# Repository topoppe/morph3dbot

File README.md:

# Morph3DBot

Willkommen im GitHub-Repo von *Morph3DBot*

Alles zu diesem Projekt finden Sie unter [https://morph3dbot.de/](https://morph3dbot.de/)

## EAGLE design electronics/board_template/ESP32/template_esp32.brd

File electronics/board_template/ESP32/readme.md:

# ESP32 Board Template

Bei der ESP32 Platine handelt es sich um eine Arduino-IDE-Kompatible Basisplatine.
Diese Platine kann sowohl als Hauptplatine im System, als auch als Slave-Platine genutzt werden.

## Spannungsversorgung
Auf der Platine sind zwei Linearregler verbaut. Sie erzeugen aus der Versorgungsspannung des Systems stabile 5V und 3,3V Spannungsversorgungen für den Controller sowie weitere Peripherie.

## Controller
Herzstück der Platine ist ein ESP32-Wroom Modul von Espressif. Es ist der selbe Controller-Typ, der auch auf Node-MCU Boards verbaut ist.
Neben den Interfaces der AT-Mega-Platine bietet das Modul auch WLAN und Bluetooth Konnektivität.

## USB-Interface
Ein CP2104 Chip verbindet die UART-Schnittstelle des Controllers mit einer USB-Buchse. Hierüber ist eine Kommunikation mit einem PC und die Programmierung mittels der Arduino-IDE möglich.

## Erweiterungsschnittstelle
Auf der Oberseite der Platine sind zwei doppelreihige Buchsenleisten mit jeweils 12-Anschlüssen vorhanden. Hier können +5V, +3,3V, Ground, UART sowie die meisten Pins des Controllers abgegriffen werden.
So ist es möglich, eigene Erweiterungen anzuschließen.

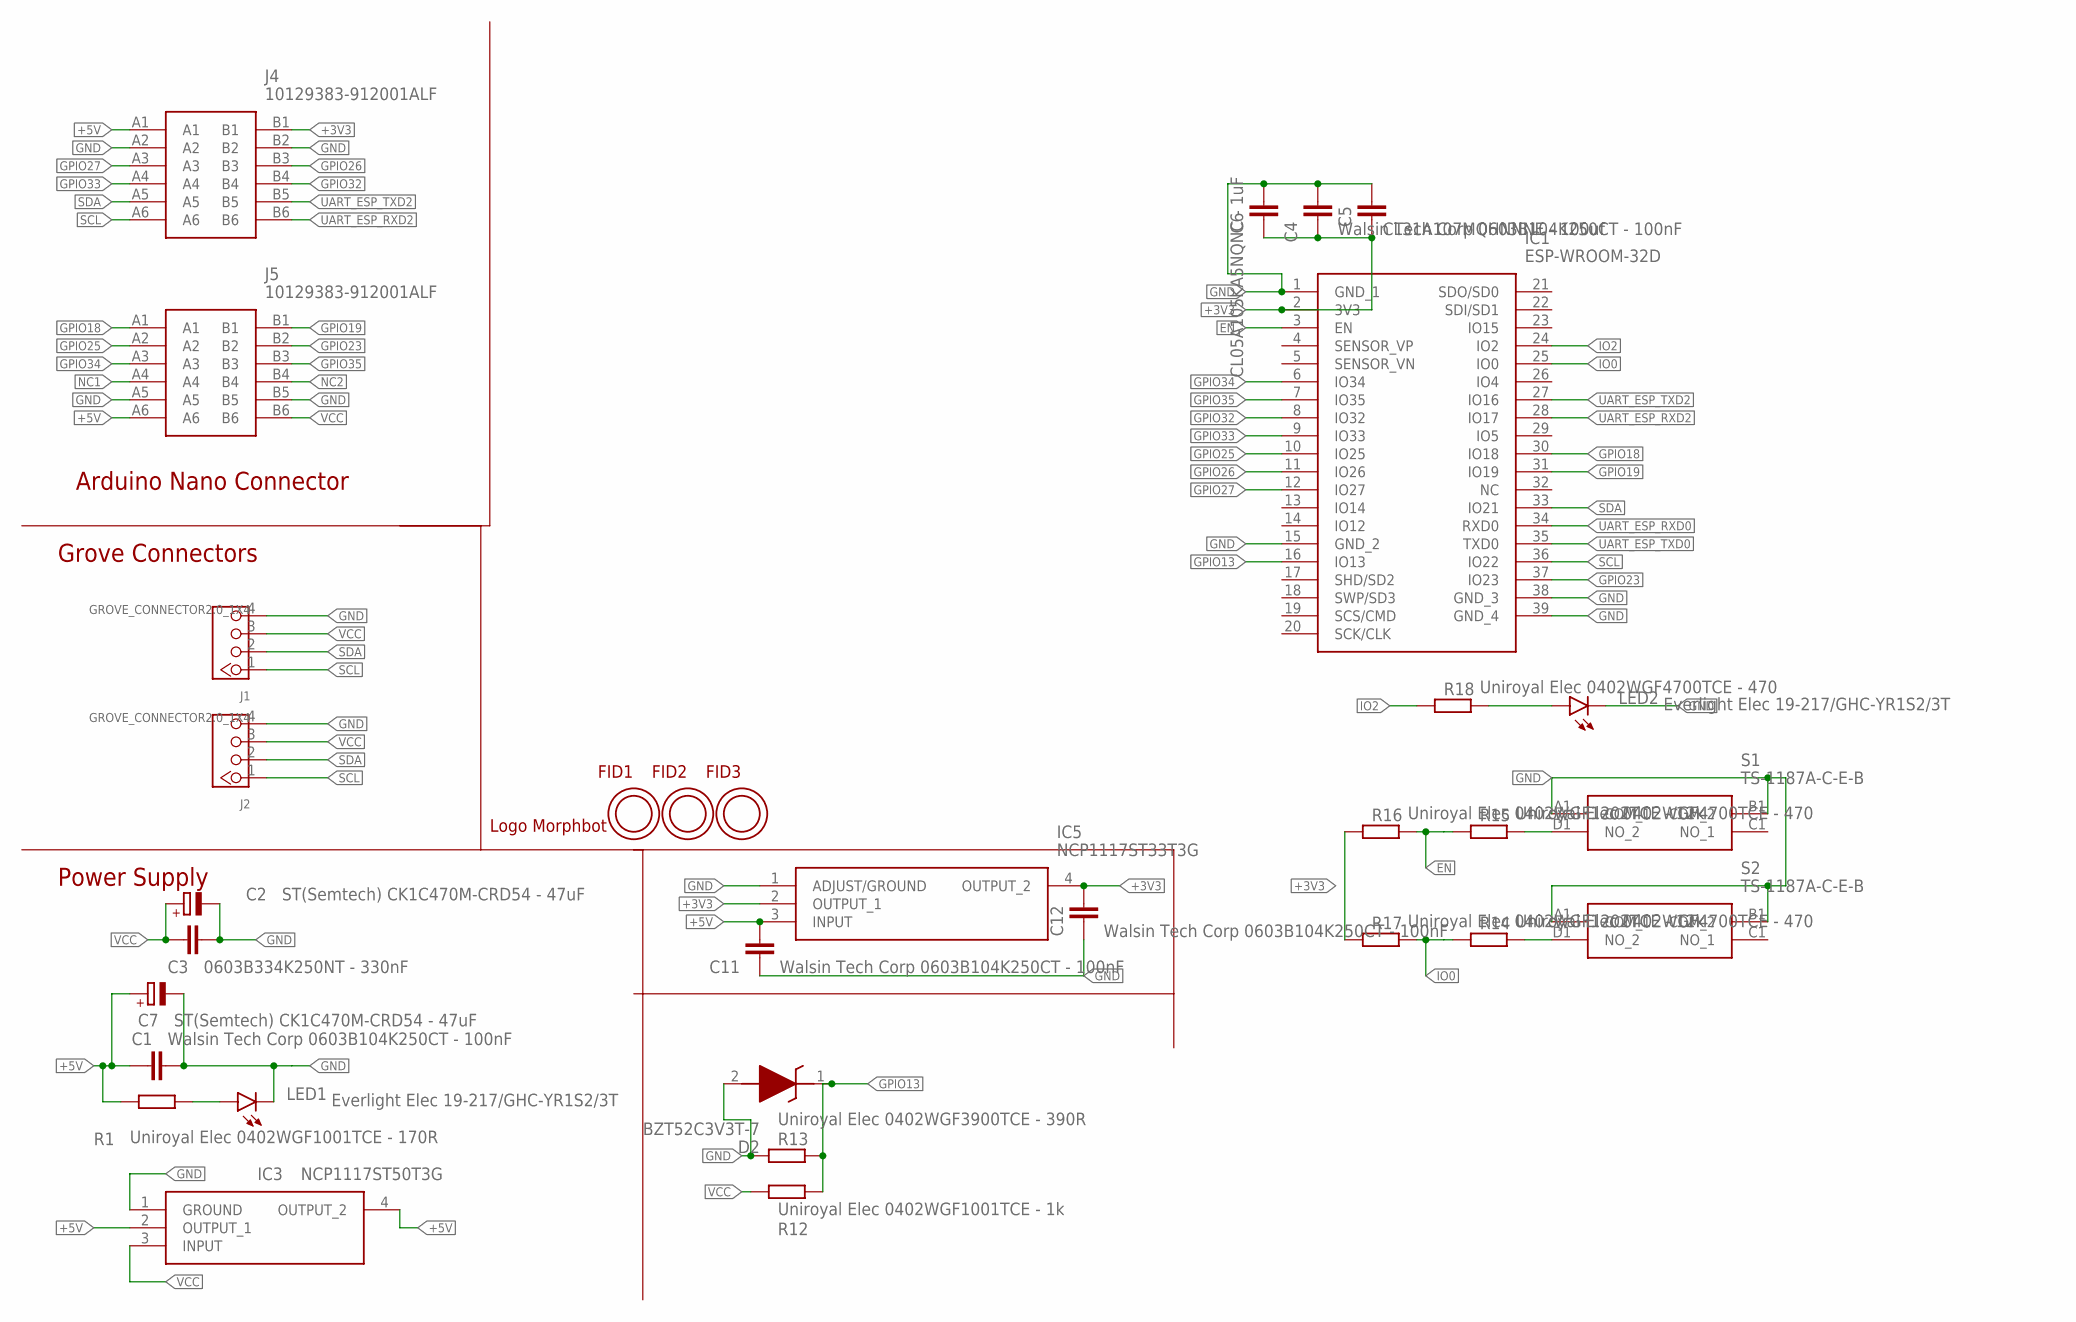
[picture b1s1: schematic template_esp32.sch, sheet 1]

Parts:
C1, C4, C11, C12: Walsin Tech Corp 0603B104K250CT - 100nF; C0603
C2, C7: ST(Semtech) CK1C470M-CRD54 - 47uF; PANASONIC_C
C3: 0603B334K250NT - 330nF; C0603
C5: CL31A107MQHNNNE - 100uf; C1206
C6: CL05A105KA5NQNC - 1uF; C0402
D2: BZT52C3V3T-7; SODFL1608X65N
FID1, FID2, FID3: OPEN-PNP-FIDUCIAL
IC1: ESP-WROOM-32D; ESPWROOM32D
IC3: NCP1117ST50T3G; SOT230P700X180-4N
IC5: NCP1117ST33T3G; SOT230P700X180-4N
J1, J2: GROVE_CONNECTOR2.0_1X4; 2.0_1X4_STRAIGHT
J4, J5: 10129383-912001ALF; 10129383912001ALF
LED1, LED2: Everlight Elec 19-217/GHC-YR1S2/3T; CHIPLED_0603
R1: Uniroyal Elec 0402WGF1001TCE - 170R; R0402
R12: Uniroyal Elec 0402WGF1001TCE - 1k; R0402
R13: Uniroyal Elec 0402WGF3900TCE - 390R; R0402
R14, R15, R18: Uniroyal Elec 0402WGF4700TCE - 470; R0402
R16, R17: Uniroyal Elec 0402WGF1202TCE - 12k; R0402
S1, S2: TS-1187A-C-E-B; TS1187ACEB
U$1: LOGO_MORPHBOT3MM; LOGO_MOPRHBOT_3MM

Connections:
+3V3: C4.1, C5.2, C6.1, C12.2, IC1.2 (3V3), IC5.2 (OUTPUT_1), IC5.4 (OUTPUT_2), J4.B1, R16.1, R17.1; also elsewhere on the board
+5V: C1.1, C7.+, C11.2, IC3.2 (OUTPUT_1), IC3.4 (OUTPUT_2), IC5.3 (INPUT), J4.A1, J5.A6, R1.2; also elsewhere on the board
EN: IC1.3 (EN), R15.1, R16.2; also elsewhere on the board
GND: C1.2, C2.-, C3.1, C4.2, C5.1, C6.2, C7.-, C11.1, C12.1, D2.2 (A), IC1.1 (GND_1), IC1.15 (GND_2), IC1.38 (GND_3), IC1.39 (GND_4), IC3.1 (GROUND), IC5.1 (ADJUST/GROUND), J1.4, J2.4, J4.A2, J4.B2, J5.A5, J5.B5, LED1.C, LED2.C, R13.1, S1.A1 (COM_1), S1.B1 (COM_2), S2.A1 (COM_1), S2.B1 (COM_2); also elsewhere on the board
GPIO13: D2.1 (K), IC1.16 (IO13), R12.1, R13.2
GPIO18: IC1.30 (IO18), J5.A1
GPIO19: IC1.31 (IO19), J5.B1
GPIO23: IC1.37 (IO23), J5.B2
GPIO25: IC1.10 (IO25), J5.A2
GPIO26: IC1.11 (IO26), J4.B3
GPIO27: IC1.12 (IO27), J4.A3
GPIO32: IC1.8 (IO32), J4.B4
GPIO33: IC1.9 (IO33), J4.A4
GPIO34: IC1.6 (IO34), J5.A3
GPIO35: IC1.7 (IO35), J5.B3
IO0: IC1.25 (IO0), R14.1, R17.2; also elsewhere on the board
IO2: IC1.24 (IO2), R18.1
unnamed: LED1.A, R1.1
unnamed: R15.2, S1.D1 (NO_2)
unnamed: R14.2, S2.D1 (NO_2)
unnamed: LED2.A, R18.2
NC1: J5.A4
NC2: J5.B4
SCL: IC1.36 (IO22), J1.1, J2.1, J4.A6
SDA: IC1.33 (IO21), J1.2, J2.2, J4.A5
UART_ESP_RXD0: IC1.34 (RXD0); also elsewhere on the board
UART_ESP_RXD2: IC1.28 (IO17), J4.B6
UART_ESP_TXD0: IC1.35 (TXD0); also elsewhere on the board
UART_ESP_TXD2: IC1.27 (IO16), J4.B5
VCC: C2.+, C3.2, IC3.3 (INPUT), J1.3, J2.3, J5.B6, R12.2; also elsewhere on the board

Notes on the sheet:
Power Supply
Grove Connectors
Arduino Nano Connector

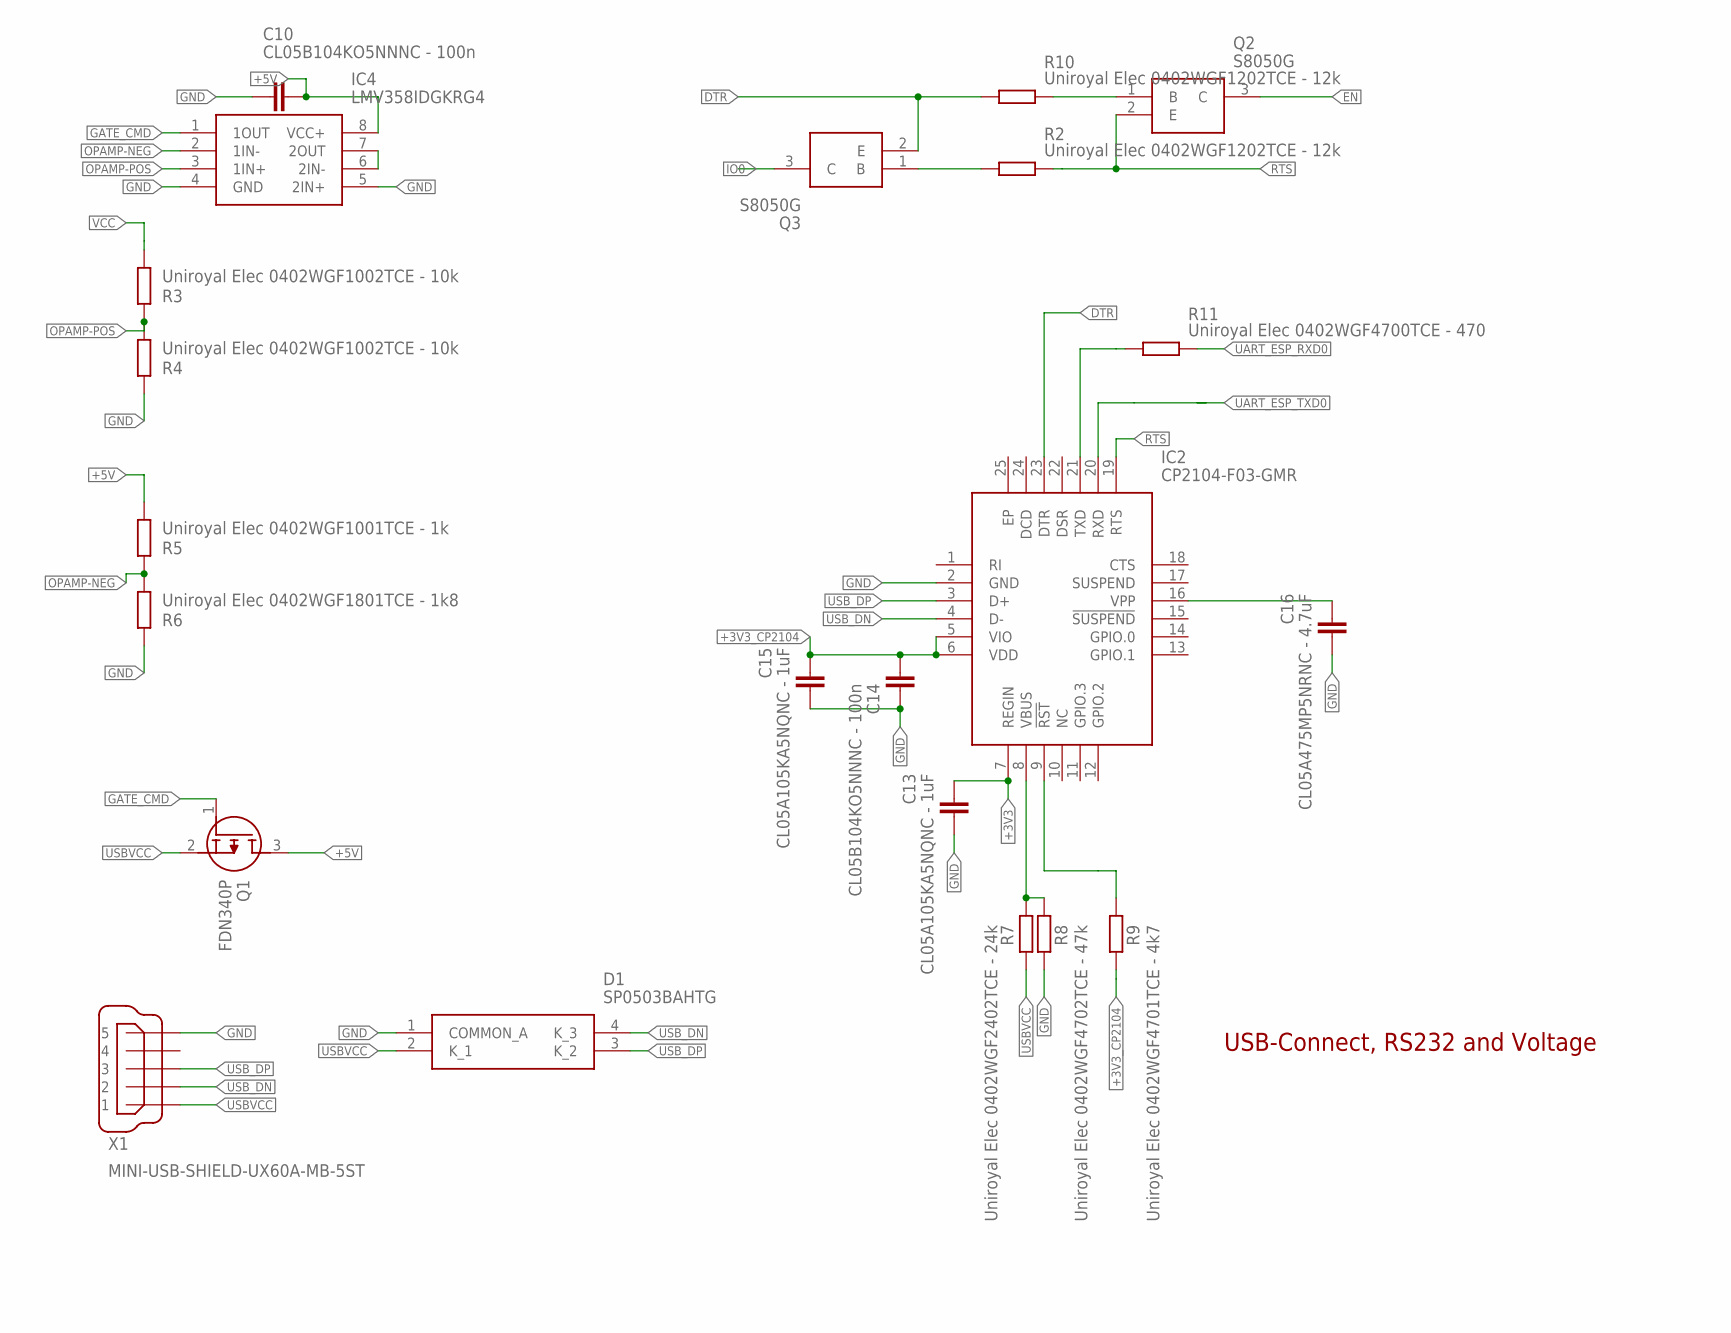
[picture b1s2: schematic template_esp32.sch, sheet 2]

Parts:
C10, C14: CL05B104KO5NNNC - 100n; C0402
C13, C15: CL05A105KA5NQNC - 1uF; C0402
C16: CL05A475MP5NRNC - 4.7uF; C0402
D1: SP0503BAHTG
IC2: CP2104-F03-GMR; QFN50P400X400X80-25N
IC4: LMV358IDGKRG4; SOP65P490X110-8N
Q1: FDN340P; SOT95P237X112-3N
Q2, Q3: S8050G; SOT95P240X110-3N
R2, R10: Uniroyal Elec 0402WGF1202TCE - 12k; R0402
R3, R4: Uniroyal Elec 0402WGF1002TCE - 10k; R0402
R5: Uniroyal Elec 0402WGF1001TCE - 1k; R0402
R6: Uniroyal Elec 0402WGF1801TCE - 1k8; R0402
R7: Uniroyal Elec 0402WGF2402TCE - 24k; R0402
R8: Uniroyal Elec 0402WGF4702TCE - 47k; R0402
R9: Uniroyal Elec 0402WGF4701TCE - 4k7; R0402
R11: Uniroyal Elec 0402WGF4700TCE - 470; R0402
X1: MINI-USB-SHIELD-UX60A-MB-5ST; UX60A-MB-5ST

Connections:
+3V3: C13.2, IC2.7 (REGIN); also elsewhere on the board
+3V3_CP2104: C14.2, C15.2, IC2.5 (VIO), IC2.6 (VDD), R9.2
+5V: C10.2, IC4.8 (VCC+), Q1.3 (D), R5.1; also elsewhere on the board
DTR: IC2.23 (DTR), Q3.2 (E), R10.1
EN: Q2.3 (C); also elsewhere on the board
GATE_CMD: IC4.1 (1OUT), Q1.1 (G)
GND: C10.1, C13.1, C14.1, C15.1, C16.1, D1.1 (COMMON_A), IC2.2 (GND), IC4.4 (GND), IC4.5 (2IN+), R4.2, R6.2, R8.2, X1.5; also elsewhere on the board
IO0: Q3.3 (C); also elsewhere on the board
unnamed: Q3.1 (B), R2.1
unnamed: IC4.6 (2IN-), IC4.7 (2OUT)
unnamed: IC2.8 (VBUS), R7.1, R8.1
unnamed: IC2.9 (!RST), R9.1
unnamed: C16.2, IC2.16 (VPP)
unnamed: IC2.21 (TXD), R11.1
unnamed: Q2.1 (B), R10.2
OPAMP-NEG: IC4.2 (1IN-), R5.2, R6.1
OPAMP-POS: IC4.3 (1IN+), R3.2, R4.1
RTS: IC2.19 (RTS), Q2.2 (E), R2.2
UART_ESP_RXD0: R11.2; also elsewhere on the board
UART_ESP_TXD0: IC2.20 (RXD); also elsewhere on the board
USBVCC: D1.2 (K_1), Q1.2 (S), R7.2, X1.1
USB_DN: D1.4 (K_3), IC2.4 (D-), X1.2
USB_DP: D1.3 (K_2), IC2.3 (D+), X1.3
VCC: R3.1; also elsewhere on the board

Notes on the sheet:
USB-Connect, RS232 and Voltage

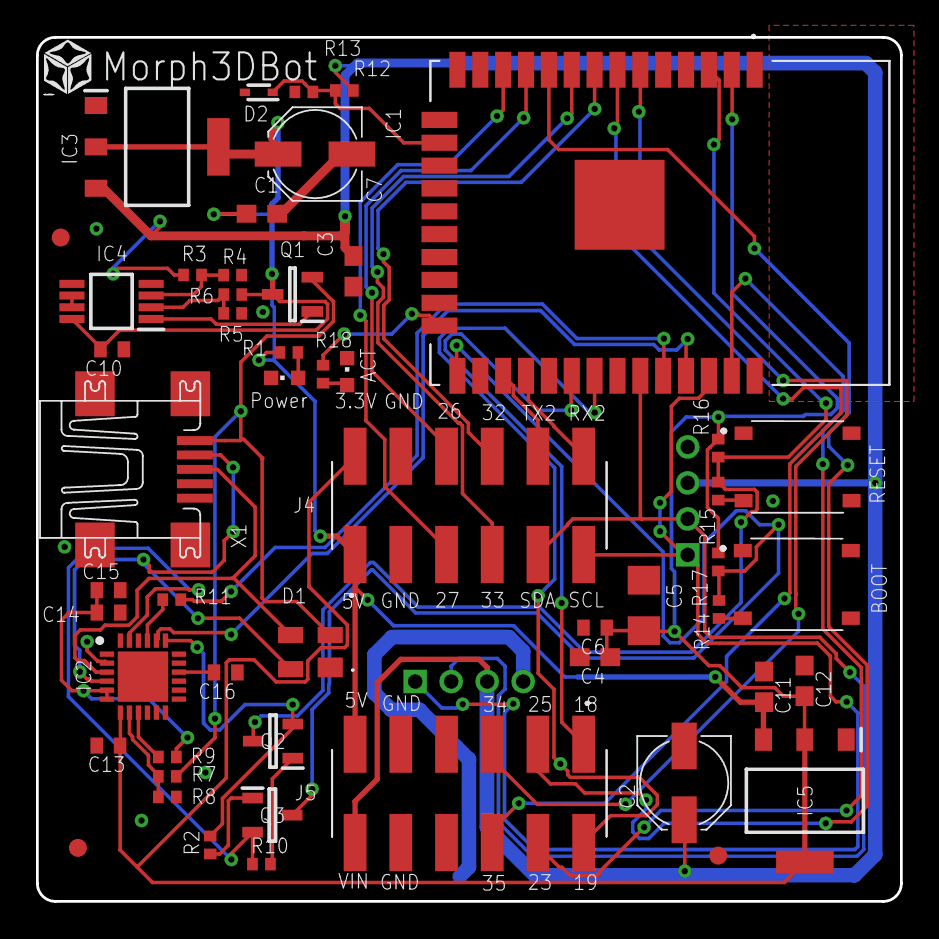
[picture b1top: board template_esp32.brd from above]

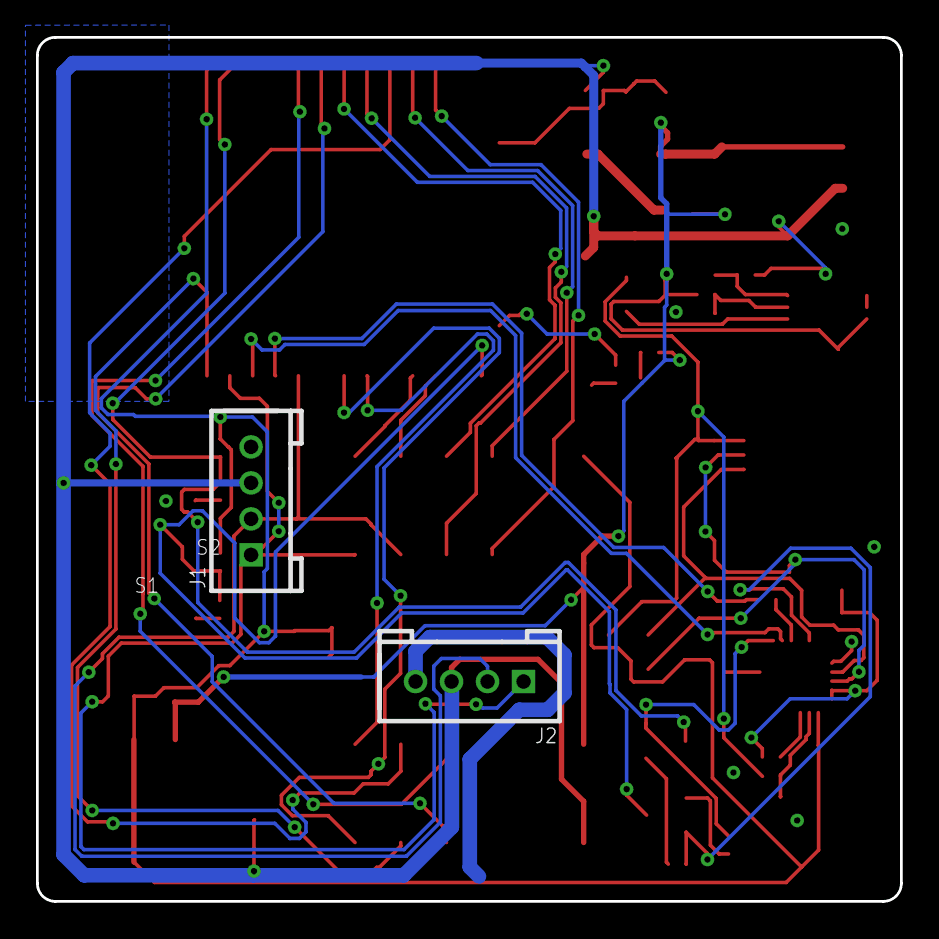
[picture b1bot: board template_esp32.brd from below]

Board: 2 copper layers, 48.0 x 48.0 mm, 55 parts (2 on the bottom side), 44 nets.

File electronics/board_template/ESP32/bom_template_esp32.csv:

"Qty";"Value";"Device";"Package";"Parts";"Description";"ARROW_PART_NUMBER";"ARROW_PRICE-STOCK";"DESCRIPTION";"HEIGHT";"MANUFACTURER_NAME";"MANUFACTURER_PART_NUMBER";"MF";"MOUSER_PART_NUMBER";"MOUSER_PRICE-STOCK";"MPN";"OC_FARNELL";"OC_NEWARK";"POPULARITY";"SPICEPREFIX";
"1";"0603B334K250NT - 330nF";"C-EUC0603";"C0603";"C3";"CAPACITOR, European symbol";"";"";"";"";"";"";"";"";"";"";"";"";"73";"C";
"2";"10129383-912001ALF";"10129383-912001ALF";"10129383912001ALF";"J4, J5";"EconoStik, Board to Board connector, Unshrouded Vertical Header, Surface Mount, Double Row,  Positions, 2.54 mm (0.100in) Pitch.";"";"";"EconoStik, Board to Board connector, Unshrouded Vertical Header, Surface Mount, Double Row,  Positions, 2.54 mm (0.100in) Pitch.";"8.58mm";"Amphenol";"10129383-912001ALF";"";"649-1012938391201ALF";"https://www.mouser.co.uk/ProductDetail/Amphenol-FCI/10129383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";"";"";"";"";"";
"1";"BZT52C3V3T-7";"BZT52C3V3T-7";"SODFL1608X65N";"D2";"Diodes Inc BZT52C3V3T-7 Zener Diode, 3.3V 6% 300 mW SMT 2-Pin SOD-523";"BZT52C3V3T-7";"https://www.arrow.com/en/products/bzt52c3v3t-7/diodes-incorporated";"Diodes Inc BZT52C3V3T-7 Zener Diode, 3.3V 6% 300 mW SMT 2-Pin SOD-523";"0.65mm";"Diodes Inc.";"BZT52C3V3T-7";"";"621-BZT52C3V3T-7";"https://www.mouser.co.uk/ProductDetail/Diodes-Incorporated/B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";"";"";"";"";"";
"3";"CL05A105KA5NQNC - 1uF";"C-EUC0402";"C0402";"C6, C13, C15";"CAPACITOR, European symbol";"";"";"";"";"";"";"";"";"";"";"";"";"18";"C";
"1";"CL05A475MP5NRNC - 4.7uF";"C-EUC0402";"C0402";"C16";"CAPACITOR, European symbol";"";"";"";"";"";"";"";"";"";"";"";"";"18";"C";
"2";"CL05B104KO5NNNC - 100n";"C-EUC0402";"C0402";"C10, C14";"CAPACITOR, European symbol";"";"";"";"";"";"";"";"";"";"";"";"";"18";"C";
"1";"CL31A107MQHNNNE - 100uf";"C-EUC1206";"C1206";"C5";"CAPACITOR, European symbol";"";"";"";"";"";"";"";"";"";"";"";"";"54";"C";
"1";"CP2104-F03-GMR";"CP2104-F03-GMR";"QFN50P400X400X80-25N";"IC2";"USB-to-UART 1-CH 576byte FIFO 3.3V Automotive 24-Pin QFN EP T/R";"CP2104-F03-GMR";"https://www.arrow.com/en/products/cp2104-f03-gmr/silicon-labs";"USB-to-UART 1-CH 576byte FIFO 3.3V Automotive 24-Pin QFN EP T/R";"0.8mm";"Silicon Labs";"CP2104-F03-GMR";"";"634-CP2104-F03-GMR";"https://www.mouser.co.uk/ProductDetail/Silicon-Labs/CP2104-F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";"";"";"";"";"";
"1";"ESP-WROOM-32D";"ESP-WROOM-32D";"ESPWROOM32D";"IC1";"WiFi Modules (802.11) ESP32-D0WD 32 Mbits, 3.3 V 40 MHz onboard antenna (18.00+/-0.10) x (25.50+/-0.10) x (3.10+/-0.10)";"";"";"WiFi Modules (802.11) ESP32-D0WD 32 Mbits, 3.3 V 40 MHz onboard antenna (18.00+/-0.10) x (25.50+/-0.10) x (3.10+/-0.10)";"3.2mm";"Espressif Systems";"ESP-WROOM-32D";"";"356-ESP-WROOM-32D";"https://www.mouser.com/Search/Refine.aspx?Keyword=356-ESP-WROOM-32D";"";"";"";"";"";
"2";"Everlight Elec 19-217/GHC-YR1S2/3T";"LEDCHIPLED_0603";"CHIPLED_0603";"LED1, LED2";"LED";"";"";"";"";"";"";"";"";"";"";"";"";"28";"";
"1";"FDN340P";"FDN340P";"SOT95P237X112-3N";"Q1";"Trans MOSFET P-CH 20V 2A 3-Pin SuperSOT";"FDN340P";"https://www.arrow.com/en/products/fdn340p/on-semiconductor";"Trans MOSFET P-CH 20V 2A 3-Pin SuperSOT";"1.12mm";"ON Semiconductor";"FDN340P";"";"512-FDN340P";"https://www.mouser.co.uk/ProductDetail/ON-Semiconductor-Fair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";"";"";"";"";"";
"2";"GROVE_CONNECTOR2.0_1X4";"GROVE_CONNECTOR2.0_1X4";"2.0_1X4_STRAIGHT";"J1, J2";"Seeedstudio Grove-Connector:";"";"";"";"";"";"";"";"";"";"";"";"";"";"";
"1";"LMV358IDGKRG4";"LMV358IDGKRG4";"SOP65P490X110-8N";"IC4";"Operational Amplifiers - Op Amps Dual Low-Voltage Rail-to-Rail Out";"LMV358IDGKRG4";"https://www.arrow.com/en/products/lmv358idgkrg4/texas-instruments";"Operational Amplifiers - Op Amps Dual Low-Voltage Rail-to-Rail Out";"1.1mm";"Texas Instruments";"LMV358IDGKRG4";"";"595-LMV358IDGKRG4";"https://www.mouser.co.uk/ProductDetail/Texas-Instruments/LMV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";"";"";"";"";"";
"1";"LOGO_MORPHBOT3MM";"LOGO_MORPHBOT3MM";"LOGO_MOPRHBOT_3MM";"U$1";"";"";"";"";"";"";"";"";"";"";"";"";"";"";"";
"1";"MINI-USB-SHIELD-UX60A-MB-5ST";"MINI-USB-SHIELD-UX60A-MB-5ST";"UX60A-MB-5ST";"X1";"MINI USB Connector";"";"";"";"";"";"";"";"";"";"";"unknown";"unknown";"0";"";
"1";"NCP1117ST33T3G";"NCP1117ST33T3G";"SOT230P700X180-4N";"IC5";"ON SEMICONDUCTOR - NCP1117ST33T3G - IC, LINEAR VOLTAGE REGULATOR";"NCP1117ST33T3G";"https://www.arrow.com/en/products/ncp1117st33t3g/on-semiconductor";"ON SEMICONDUCTOR - NCP1117ST33T3G - IC, LINEAR VOLTAGE REGULATOR";"1.8mm";"ON Semiconductor";"NCP1117ST33T3G";"";"863-NCP1117ST33T3G";"https://www.mouser.co.uk/ProductDetail/ON-Semiconductor/NCP1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";"";"";"";"";"";
"1";"NCP1117ST50T3G";"NCP1117ST50T3G";"SOT230P700X180-4N";"IC3";"ON SEMICONDUCTOR - NCP1117ST50T3G - LDO, REG, 20VIN, 1A, 5V, 1%, SOT223-3";"NCP1117ST50T3G";"https://www.arrow.com/en/products/ncp1117st50t3g/on-semiconductor";"ON SEMICONDUCTOR - NCP1117ST50T3G - LDO, REG, 20VIN, 1A, 5V, 1%, SOT223-3";"1.8mm";"ON Semiconductor";"NCP1117ST50T3G";"";"863-NCP1117ST50T3G";"https://www.mouser.co.uk/ProductDetail/ON-Semiconductor/NCP1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";"";"";"";"";"";
"3";"OPEN-PNP-FIDUCIAL";"OPEN-PNP-FIDUCIAL";"OPEN-PNP-FIDUCIAL";"FID1, FID2, FID3";"";"";"";"";"";"";"";"";"";"";"";"";"";"";"";
"2";"S8050G";"S8050G";"SOT95P240X110-3N";"Q2, Q3";"Silicon Epitaxial Planar Transistor";"";"";"Silicon Epitaxial Planar Transistor";"1.1mm";"Galaxy";"S8050G";"";"";"";"";"";"";"";"";
"1";"SP0503BAHTG";"SP0503BAHTG";"SP0503BAHTG";"D1";"ESD Suppressors / TVS Diodes TVS AVAL DIODE SMT";"SP0503BAHTG";"https://www.arrow.com/en/products/sp0503bahtg/littelfuse";"ESD Suppressors / TVS Diodes TVS AVAL DIODE SMT";"1.22mm";"LITTELFUSE";"SP0503BAHTG";"";"576-SP0503BAHTG";"https://www.mouser.co.uk/ProductDetail/Littelfuse/SP0503BAHT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";"";"";"";"";"";
"2";"ST(Semtech) CK1C470M-CRD54 - 47uF";"CPOL-EUC";"PANASONIC_C";"C2, C7";"POLARIZED CAPACITOR, European symbol";"";"";"";"";"";"";"";"";"";"";"";"";"4";"C";
"2";"TS-1187A-C-E-B";"TS-1187A-C-E-B";"TS1187ACEB";"S1, S2";"SPST 50mA @ 12VDC 5.10mm x 5.10mm SMD Tactile Switches RoHS";"";"";"SPST 50mA @ 12VDC 5.10mm x 5.10mm SMD Tactile Switches RoHS";"1.65mm";"XKB Enterprise";"TS-1187A-C-E-B";"";"";"";"";"";"";"";"";
"1";"Uniroyal Elec 0402WGF1001TCE - 170R";"R-EU_R0402";"R0402";"R1";"RESISTOR, European symbol";"";"";"";"";"";"";"";"";"";"";"";"";"0";"R";
"2";"Uniroyal Elec 0402WGF1001TCE - 1k";"R-EU_R0402";"R0402";"R5, R12";"RESISTOR, European symbol";"";"";"";"";"";"";"";"";"";"";"";"";"0";"R";
"2";"Uniroyal Elec 0402WGF1002TCE - 10k";"R-EU_R0402";"R0402";"R3, R4";"RESISTOR, European symbol";"";"";"";"";"";"";"";"";"";"";"";"";"0";"R";
"4";"Uniroyal Elec 0402WGF1202TCE - 12k";"R-EU_R0402";"R0402";"R2, R10, R16, R17";"RESISTOR, European symbol";"";"";"";"";"";"";"";"";"";"";"";"";"0";"R";
"1";"Uniroyal Elec 0402WGF1801TCE - 1k8";"R-EU_R0402";"R0402";"R6";"RESISTOR, European symbol";"";"";"";"";"";"";"";"";"";"";"";"";"0";"R";
"1";"Uniroyal Elec 0402WGF2402TCE - 24k";"R-EU_R0402";"R0402";"R7";"RESISTOR, European symbol";"";"";"";"";"";"";"";"";"";"";"";"";"0";"R";
"1";"Uniroyal Elec 0402WGF3900TCE - 390R";"R-EU_R0402";"R0402";"R13";"RESISTOR, European symbol";"";"";"";"";"";"";"";"";"";"";"";"";"0";"R";
"4";"Uniroyal Elec 0402WGF4700TCE - 470";"R-EU_R0402";"R0402";"R11, R14, R15, R18";"RESISTOR, European symbol";"";"";"";"";"";"";"";"";"";"";"";"";"0";"R";
"1";"Uniroyal Elec 0402WGF4701TCE - 4k7";"R-EU_R0402";"R0402";"R9";"RESISTOR, European symbol";"";"";"";"";"";"";"";"";"";"";"";"";"0";"R";
"1";"Uniroyal Elec 0402WGF4702TCE - 47k";"R-EU_R0402";"R0402";"R8";"RESISTOR, European symbol";"";"";"";"";"";"";"";"";"";"";"";"";"0";"R";
"4";"Walsin Tech Corp 0603B104K250CT - 100nF";"C-EUC0603";"C0603";"C1, C4, C11, C12";"CAPACITOR, European symbol";"";"";"";"";"";"";"";"";"";"";"";"";"73";"C";

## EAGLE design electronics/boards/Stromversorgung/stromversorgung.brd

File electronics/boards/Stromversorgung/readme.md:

# Stromversorgungsplatine

**Diese Platine darf und muss genau einmal im System verbaut werden!**

Diese Platine dient zum Anschluss einer Stromquelle an das *Morph3DBot*-System. Hierzu dient eine Doppelschraubklemme auf der Oberseite der Platine.
Es können Spannungen bis zu 16 Volt eingespeist werden, es wird jedoch mindestens eine Spannung von 7 Volt benötigt.

Außerdem sind auf dieser Platine die Pull-Up-Widerstände für den I2C-Bus verbaut.

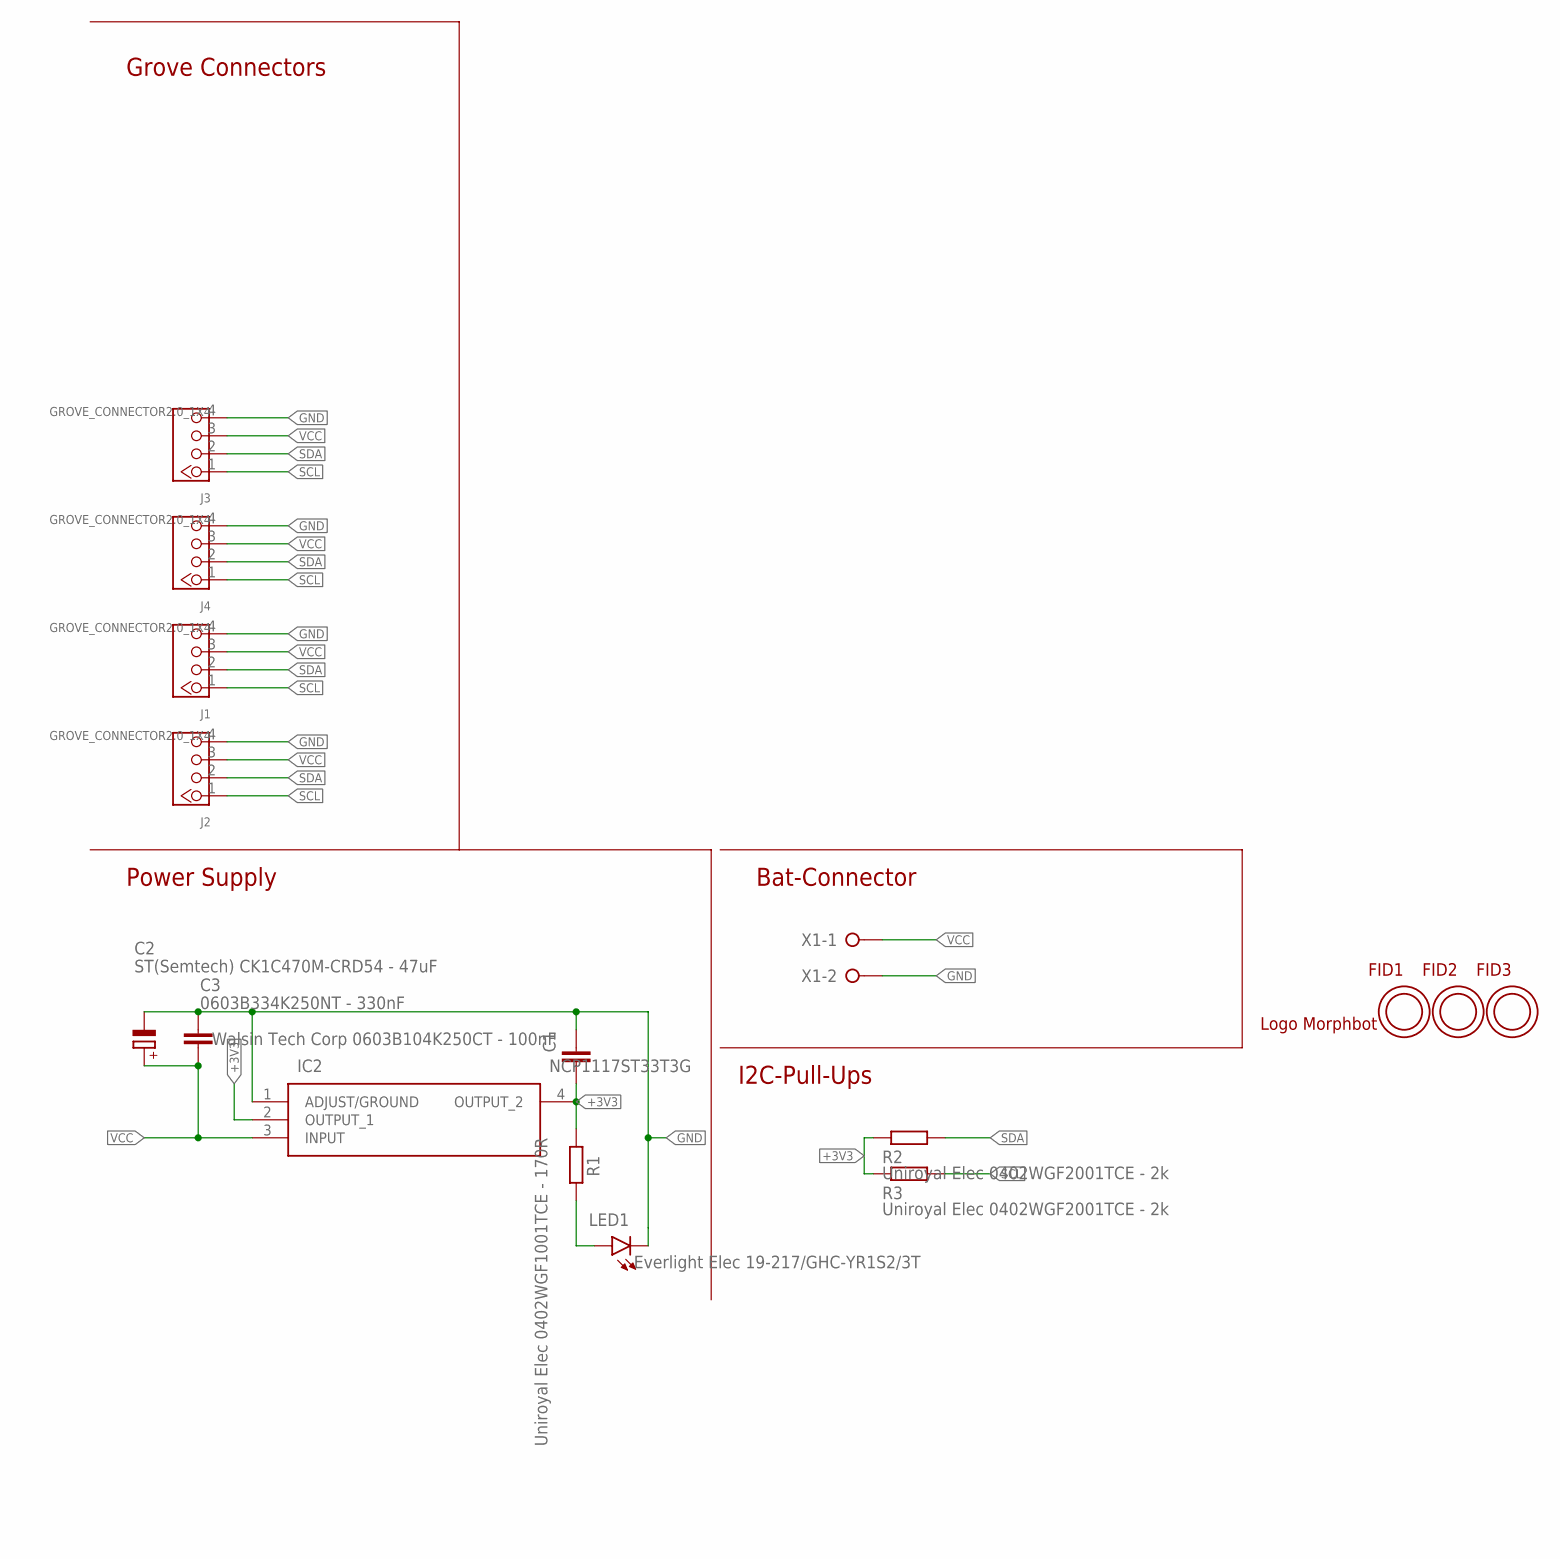
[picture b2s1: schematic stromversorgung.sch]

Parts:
C1: Walsin Tech Corp 0603B104K250CT - 100nF; C0603
C2: ST(Semtech) CK1C470M-CRD54 - 47uF; PANASONIC_C
C3: 0603B334K250NT - 330nF; C0603
FID1, FID2, FID3: OPEN-PNP-FIDUCIAL
IC2: NCP1117ST33T3G; SOT230P700X180-4N
J1, J2, J3, J4: GROVE_CONNECTOR2.0_1X4; 2.0_1X4_STRAIGHT
LED1: Everlight Elec 19-217/GHC-YR1S2/3T; CHIPLED_0603
R1: Uniroyal Elec 0402WGF1001TCE - 170R; R0402
R2, R3: Uniroyal Elec 0402WGF2001TCE - 2k; R0402
U$1: LOGO_MORPHBOT5MM; LOGO_MORPHBOT
X1: W237-02P; W237-132

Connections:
+3V3: C1.1, IC2.2 (OUTPUT_1), IC2.4 (OUTPUT_2), R1.2, R2.2, R3.2
GND: C1.2, C2.-, C3.1, IC2.1 (ADJUST/GROUND), J1.4, J2.4, J3.4, J4.4, LED1.C, X1.2
unnamed: LED1.A, R1.1
SCL: J1.1, J2.1, J3.1, J4.1, R3.1
SDA: J1.2, J2.2, J3.2, J4.2, R2.1
VCC: C2.+, C3.2, IC2.3 (INPUT), J1.3, J2.3, J3.3, J4.3, X1.1

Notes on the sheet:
Power Supply
Grove Connectors
I2C-Pull-Ups
Bat-Connector

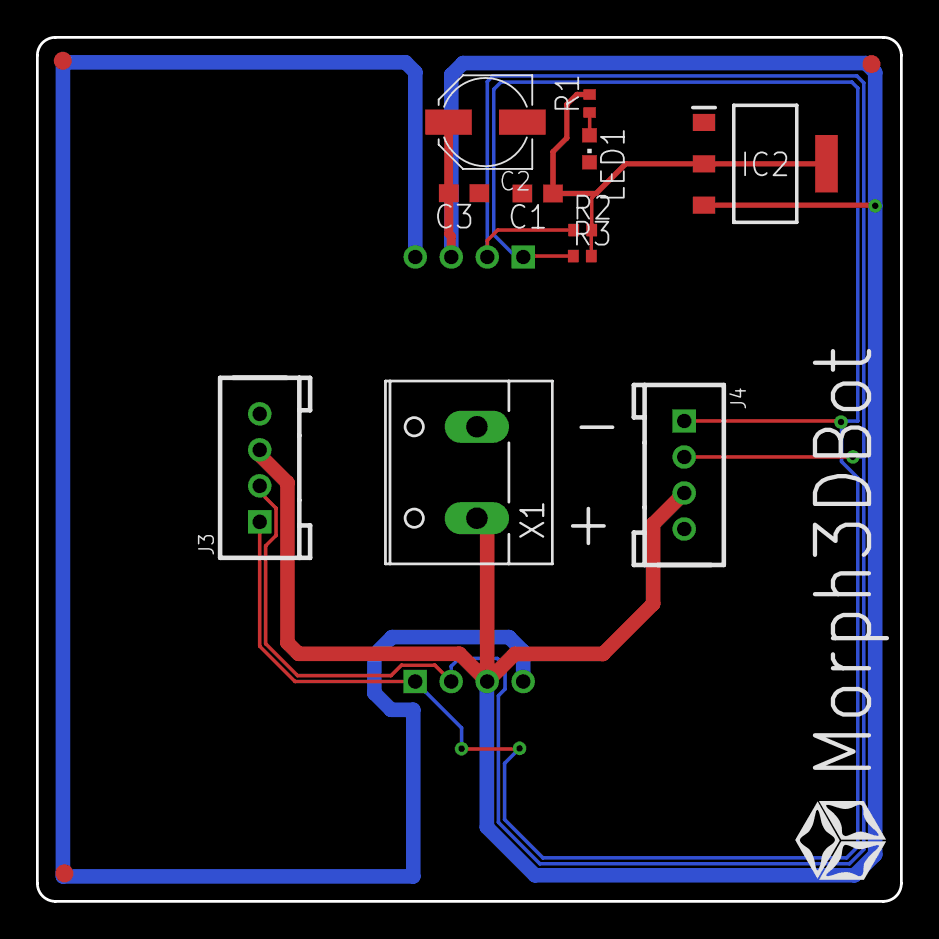
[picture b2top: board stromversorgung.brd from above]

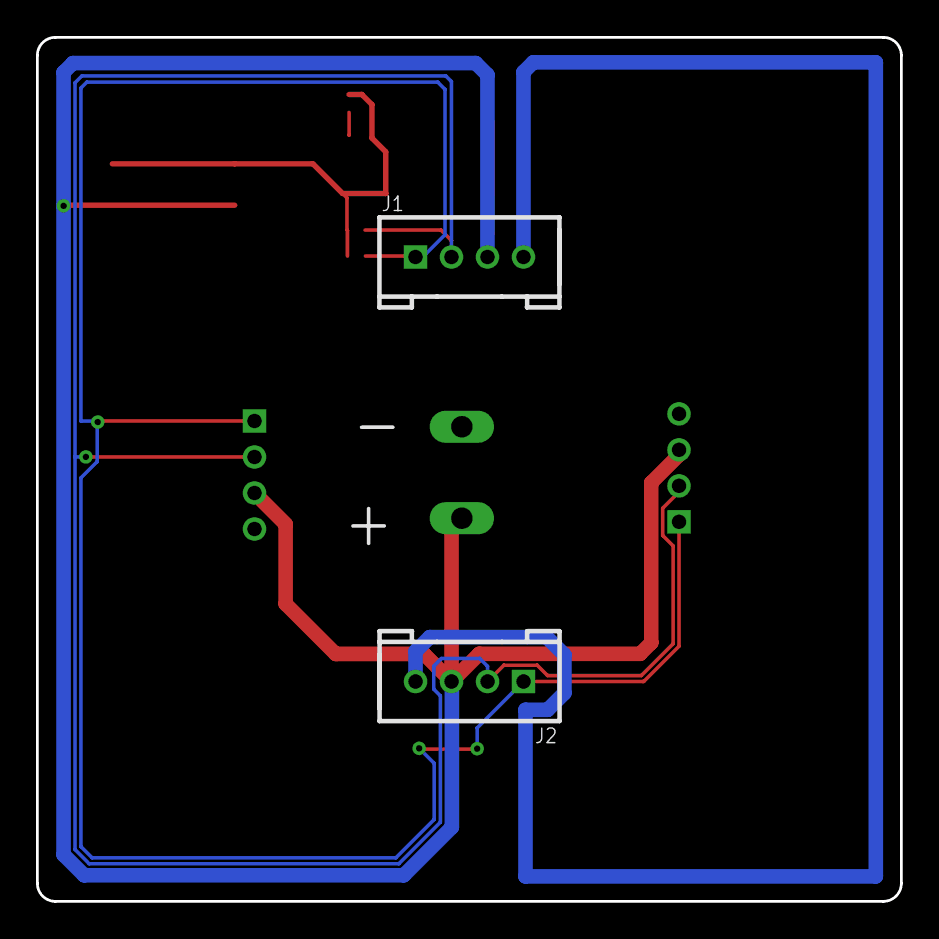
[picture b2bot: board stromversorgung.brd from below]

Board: 2 copper layers, 48.0 x 48.0 mm, 17 parts (2 on the bottom side), 6 nets.
